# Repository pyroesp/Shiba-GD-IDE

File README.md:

# Shiba GD-IDE

The Sega Dreamcast uses a GD-ROM Optical Drive to read the game discs. Some clever people discovered that the optical drive uses connections similar to an IDE HDD.  
If you look for *Dreamcast HDD mod* on Google Images you'll see some crazy stuff. People were just soldering 40 pin flat ribbon cables to the motherboard or optical drive directly, which looks pretty cool to be honest.  

Some guys designed the GD-IDE which is a PCB, which is soldered on top of the optical drive of the Dreamcast, that allows you to plug in an IDE HDD.  
The Shiba GD-IDE is a complete redesign of GD-IDE board for the Toshiba GD-ROM Optical Drive.  

The name *Shiba GD-IDE* comes from the fact that the GD-ROM optical drive has a To**shiba** chip on it and the name of the original board. 

The original GD-IDE is designed by tawy / DragonCity.  
You can find the GD-IDE on DragonCity's webpage here: [Dreamcast GD-IDE](https://boutique-dragoncity.myshopify.com/collections/dreamcast/products/dreamcast-pcb-dreamcast-gd-ide-v3-connecteur-ide)

## Disclaimer

Obviously, I'm not responsible if this breaks your GD-ROM drive.  
At the time of writing (21/08/2020) the boards have not yet been tested.

## Compatible GD-ROM

The Shiba GD-IDE is only compatible with GD-ROM drive that have a Toshiba IC on top, like shown below.  

## Shiba GD-IDE PCB

If you're going to buy some boards directly from a PCB fab, change the width of the board to 1mm.  
I'm using JLCPCB to make my boards and that's why I have added 'JLCJLCJLCJLC' on to the board as a place holder for their order number.  
It's kind of hidden under the 40 pin header, which is where I want it.  

Just like on the GD-IDE, you want to remove pin 20 from the header pins, to make it fit with DragonCity's ribbon cable.  

KiCad 3D model:  

FreeCAD 3D model:  

## GD-ROM drive Connector

The connector is apparently a Molex 0525840579 that you can find on digikey.  
I got the names of the Molex connections from the schematics found on [console5.com](https://console5.com/wiki/Dreamcast).  
  
The connections from the Molex connector to the IDE HDD I got from DragonCity's image below.  
  
*Note: I have added the smaller numbers into the two columns to make it easier for me to map

All pinouts, pin names and connections to test points can be found in the text file in the docs folder, which looks like this:  
> ...
> 
> IDE HDD to Dreamcast GD-ROM TP:
> -------------------------------
> IDE 1 - ~RESET		A2		TP226 (not needed but provide bridge, see install tutorial GD-IDE from Dragoncity.fr)  
> IDE 2 - GND		A8/GND  
> IDE 3 - HD7		A4		TP229  
> IDE 4 - HD8		A5		TP231  
> IDE 5 - HD6		B4		TP230  
> ...  

## BOM

- PCB from any PCB fab you want. I personnaly use JLCPCB as they're cheap.  
- IDE flat ribbon cable, like the one sold by DragonCity here: [IDE cable](https://boutique-dragoncity.myshopify.com/collections/dreamcast/products/nappe-ide-80-pins-ata-133)  
- Optional: [IDE to SATA adapter](https://boutique-dragoncity.myshopify.com/collections/dreamcast/products/adaptateur-ide-sata-jm20330-jp103-5) also sold by DragonCity  

## License

CC BY 4.0  
See LICENSE.md

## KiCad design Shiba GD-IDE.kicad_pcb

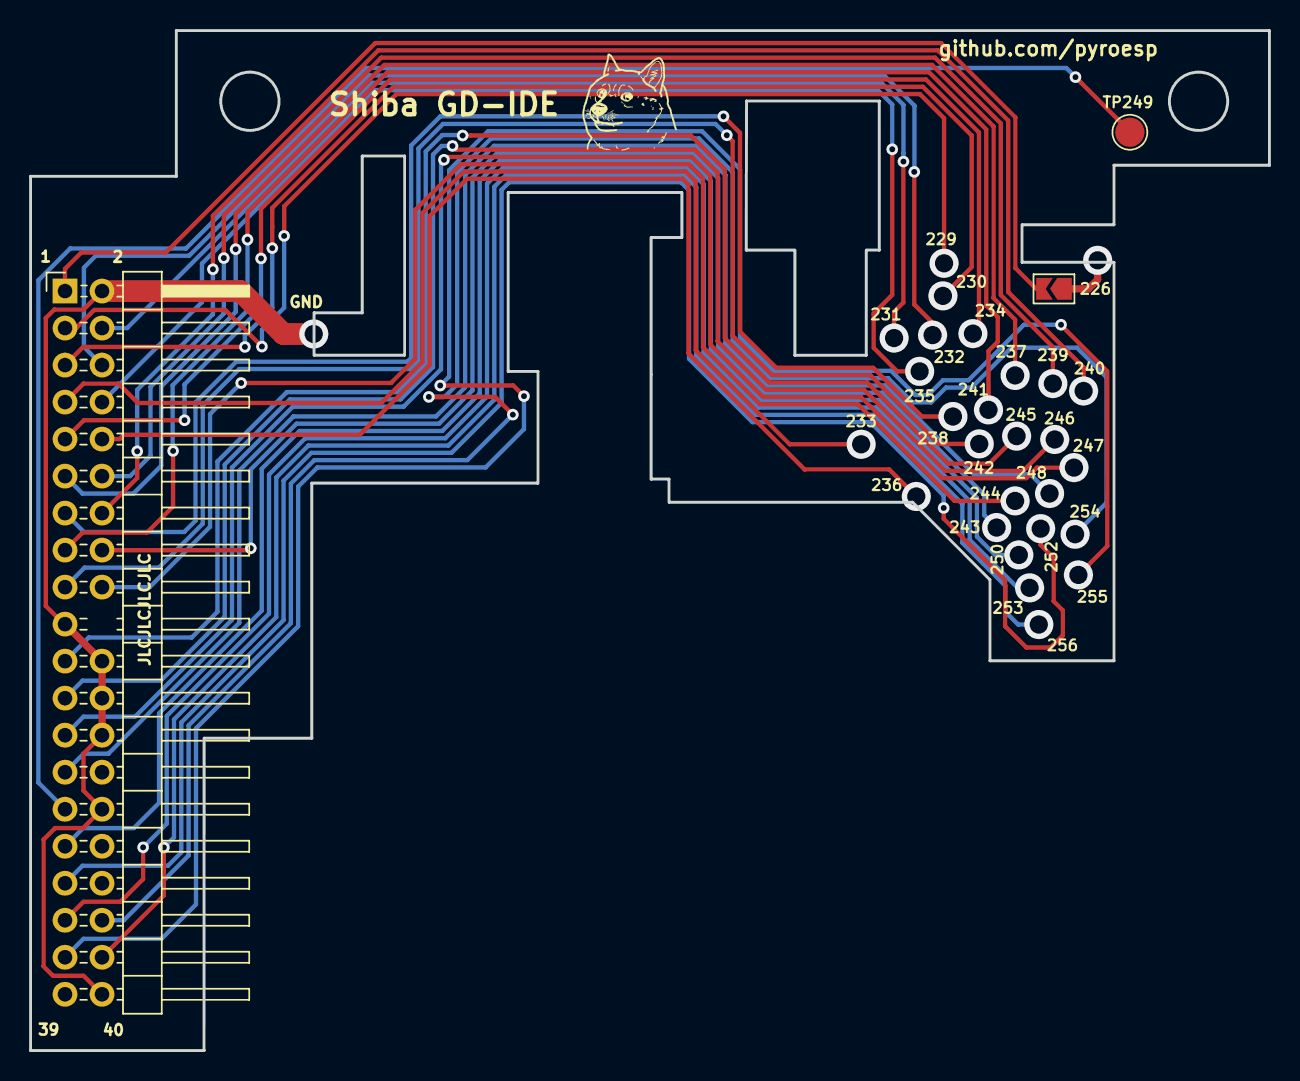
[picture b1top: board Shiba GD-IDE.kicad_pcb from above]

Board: 2 copper layers, 85.0 x 70.0 mm, 3 parts (0 on the bottom side), 3 nets.

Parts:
J1: Conn_02x20_Odd_Even; PinHeader_2x20_P2.54mm_Horizontal
J2: SolderJumper-2_P1.3mm_Open_TrianglePad1.0x1.5mm
TP249: TestPoint_Pad_D2.0mm

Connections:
GND: J1.2, J1.19, J1.22, J1.24, J1.26, J1.30, J1.40
TP226: J1.1, J2.2
TP249: J1.29, TP249.1

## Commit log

2020-08-21 updated gitignore
2020-08-21 Shiba GD-IDE first commit
2020-08-21 gerber files first commit
2020-08-21 added zip file to gitignore
2020-08-21 added license CC BY 4.0
2020-08-21 added freecad files
2020-08-21 Toshiba GD-ROM board picture
2020-08-21 GD-ROM Molex connector pinout from DragonCity
2020-08-21 Toshiba GD-ROM pinout documentation
2020-08-21 updated freecad model
2020-08-21 updated gitignore for freecad backup files
2020-08-21 added pics of the Shiba GB-IDE PCB
2020-08-22 updated readme again
